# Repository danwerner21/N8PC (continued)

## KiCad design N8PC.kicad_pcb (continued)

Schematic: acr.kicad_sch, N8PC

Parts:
R5: 470; STD_DDW_RESISTOR
U32: 74LS139; STD_DDW_DIP16
U39: 74LS04; STD_DDW_DIP14
U55: 74LS273; STD_DDW_DIP20
U70: 74LS174; STD_DDW_DIP16

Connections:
+5V: U55.20 (VCC), U70.16 (VCC); also elsewhere on the board
A1: U32.13 (A1); also elsewhere on the board
A15_ROM: U70.2 (Q0); also elsewhere on the board
A16_ROM: U70.5 (Q1); also elsewhere on the board
A17_ROM: U70.7 (Q2); also elsewhere on the board
A18_ROM: U70.10 (Q3); also elsewhere on the board
A19_ROM: U70.12 (Q4); also elsewhere on the board
ACR5: U55.15 (Q5); also elsewhere on the board
D0: U55.3 (D0), U70.3 (D0); also elsewhere on the board
D1: U55.4 (D1), U70.4 (D1); also elsewhere on the board
D2: U55.7 (D2), U70.6 (D2); also elsewhere on the board
D3: U55.8 (D3), U70.11 (D3); also elsewhere on the board
D4: U55.13 (D4), U70.13 (D4); also elsewhere on the board
D5: U55.14 (D5); also elsewhere on the board
D6: U55.17 (D6); also elsewhere on the board
D7: U55.18 (D7), U70.14 (D5); also elsewhere on the board
EXT-RES: U55.1 (~Mr), U70.1 (~Mr); also elsewhere on the board
GND: U55.10 (GND), U70.8 (GND); also elsewhere on the board
LED0: U55.2 (Q0); also elsewhere on the board
LED1: U55.5 (Q1); also elsewhere on the board
LED2: U55.6 (Q2); also elsewhere on the board
LED3: U70.15 (Q5); also elsewhere on the board
unnamed: R5.1, U39.4
unnamed: U32.12 (O0), U55.11 (Cp)
unnamed: U32.10 (O2), U70.9 (Cp)
RTS_TTL1: U55.16 (Q6); also elsewhere on the board
STATUS-LED: R5.2; also elsewhere on the board
/ACRCS: U32.15 (E); also elsewhere on the board
/RESAY3: U55.12 (Q4); also elsewhere on the board
/ROM_ENABLE: U55.19 (Q7); also elsewhere on the board
/STATUS: U39.3, U55.9 (Q3)
/WR: U32.14 (A0); also elsewhere on the board

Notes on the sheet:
STATUS LED
AUXILIARY CONTROL REGISTER

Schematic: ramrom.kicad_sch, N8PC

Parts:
K3, K4, K5, K16, K18: CONN_3; STD_DDW_PINHEAD_V_1x03
U13: 27C080; STD_DDW_DIP32
U53: SRAM_512KO; STD_DDW_DIP32

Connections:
+5V: K3.3, K16.3, K18.3, U13.32 (VCC), U53.32 (VCC); also elsewhere on the board
A0: U13.12 (A0), U53.12 (A0); also elsewhere on the board
A1: U13.11 (A1), U53.11 (A1); also elsewhere on the board
A2: U13.10 (A2), U53.10 (A2); also elsewhere on the board
A3: U13.9 (A3), U53.9 (A3); also elsewhere on the board
A4: U13.8 (A4), U53.8 (A4); also elsewhere on the board
A5: U13.7 (A5), U53.7 (A5); also elsewhere on the board
A6: U13.6 (A6), U53.6 (A6); also elsewhere on the board
A7: U13.5 (A7), U53.5 (A7); also elsewhere on the board
A8: U13.27 (A8), U53.27 (A8); also elsewhere on the board
A9: U13.26 (A9), U53.26 (A9); also elsewhere on the board
A10: U13.23 (A10), U53.23 (A10); also elsewhere on the board
A11: U13.25 (A11), U53.25 (A11); also elsewhere on the board
A12: U13.4 (A12), U53.4 (A12); also elsewhere on the board
A13: U13.28 (A13), U53.28 (A13); also elsewhere on the board
A14: U13.29 (A14), U53.3 (A14); also elsewhere on the board
A15: U53.31 (A15); also elsewhere on the board
A15_ROM: K18.1; also elsewhere on the board
A16: U53.2 (A16); also elsewhere on the board
A16_ROM: U13.2 (A16); also elsewhere on the board
A17: K16.1; also elsewhere on the board
A17_ROM: K3.1; also elsewhere on the board
A18: U53.1 (A18); also elsewhere on the board
A18_ROM: K4.1, K5.3; also elsewhere on the board
A19_ROM: K5.1; also elsewhere on the board
D0: U13.13 (D0), U53.13 (DQ0); also elsewhere on the board
D1: U13.14 (D1), U53.14 (DQ1); also elsewhere on the board
D2: U13.15 (D2), U53.15 (DQ2); also elsewhere on the board
D3: U13.17 (D3), U53.17 (DQ3); also elsewhere on the board
D4: U13.18 (D4), U53.18 (DQ4); also elsewhere on the board
D5: U13.19 (D5), U53.19 (DQ5); also elsewhere on the board
D6: U13.20 (D6), U53.20 (DQ6); also elsewhere on the board
D7: U13.21 (D7), U53.21 (DQ7); also elsewhere on the board
GND: U13.16 (GND), U53.16 (VSS); also elsewhere on the board
unnamed: K3.2, U13.30 (A17)
unnamed: K4.2, U13.31 (A18)
unnamed: K5.2, U13.1 (A19)
unnamed: K16.2, U53.30 (A17)
unnamed: K18.2, U13.3 (A15)
/CS_RAMLO: U53.22 (CE#); also elsewhere on the board
/CS_ROM: U13.22 (~CE); also elsewhere on the board
/RD: U13.24 (~OE), U53.24 (OE#); also elsewhere on the board
/WR: K4.3, U53.29 (WE#); also elsewhere on the board

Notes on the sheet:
K3 = USE FOR 32 PIN EPROM OR 28 PIN EPROM K4 = USE FOR 27C080 EPROM OR 29C040 FLASH K5 = USE FOR 27C080 EPROM OR 29C040 FLASH K18 = USE FOR 32 PIN EPROM OR 28 PIN EPROM
K16 = USE FOR 512K SRAM OR 128K SRAM

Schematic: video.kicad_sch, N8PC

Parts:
C34: 4.7pF; STD_DDW_CAP
D5: 1N5817; STD_DDW_DIODE
J11: F18A TANG NANO Connector; STD_DDW_PinHeader_2x10
U18: 74LS32; STD_DDW_DIP14
U23: TMS9918 EMU; STD_DDW_DIP40

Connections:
+5V: D5.2 (A), U23.33 (VCC); also elsewhere on the board
A0: C34.1, J11.14, U23.13 (MODE); also elsewhere on the board
D0: J11.19, U23.17 (CD7); also elsewhere on the board
D1: J11.17, U23.18 (CD6); also elsewhere on the board
D2: J11.15, U23.19 (CD5); also elsewhere on the board
D3: J11.13, U23.20 (CD4); also elsewhere on the board
D4: J11.11, U23.21 (CD3); also elsewhere on the board
D5: J11.9, U23.22 (CD2); also elsewhere on the board
D6: J11.7, U23.23 (CD1); also elsewhere on the board
D7: J11.5, U23.24 (CD0); also elsewhere on the board
EXT-RES: J11.12, U23.34 (~RESET); also elsewhere on the board
GND: C34.2, J11.1, J11.3, U23.12 (GND); also elsewhere on the board
unnamed: D5.1 (K), J11.2
VRY: J11.4, U23.38 (CPUCLK); also elsewhere on the board
/RD: U18.13; also elsewhere on the board
/VDPCS: U18.9, U18.12; also elsewhere on the board
/VDPRD: J11.18, U18.11, U23.15 (~CSR)
/VDPWR: J11.16, U18.8, U23.14 (~CSW)
/VINT: U23.16 (~INT); also elsewhere on the board
/WR: U18.10; also elsewhere on the board

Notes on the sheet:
Connector for Tang Nano F18A emulator https://github.com/lfantoniosi/tn_vdp
TMS9918 Socket, suitable for a Pico99 or F18A TMS9918 emulator Not suitable for an actual TMS9918 chip.

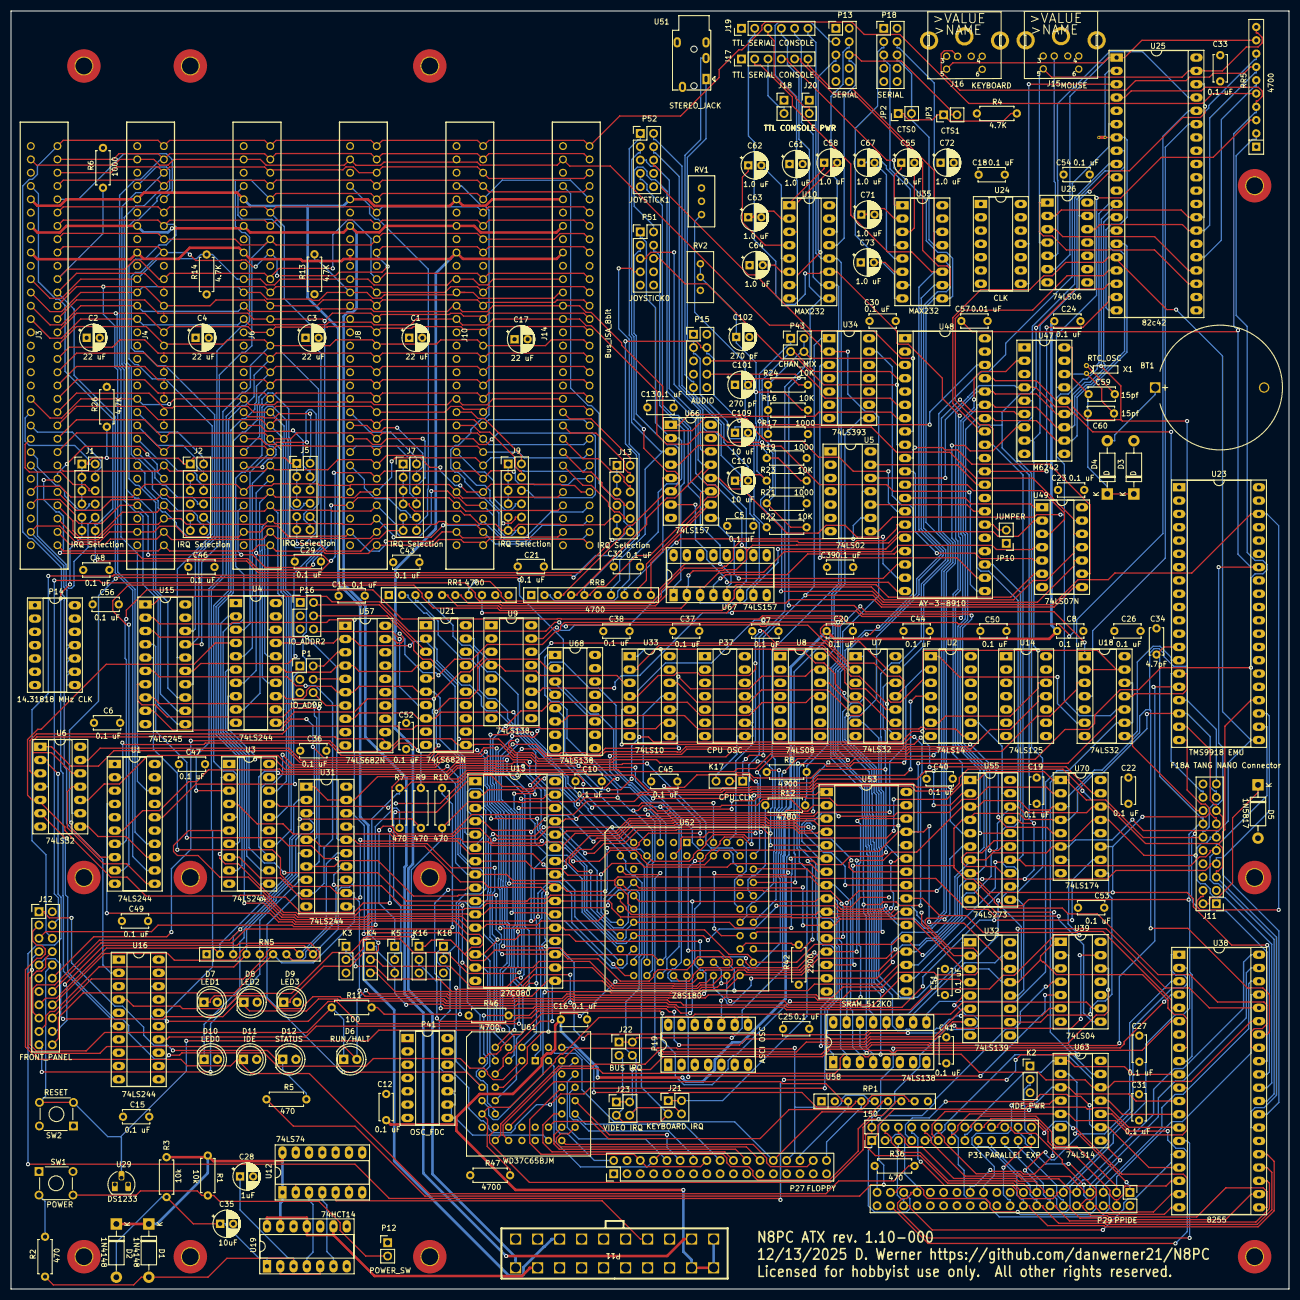
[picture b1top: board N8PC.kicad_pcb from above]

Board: 4 copper layers, 244.0 x 244.0 mm, 226 parts (0 on the bottom side), 364 nets.

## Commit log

2025-11-03 n8pc
2025-11-30 rev 1.0
2025-12-14 V1.1 PCB and schematic fix issue with data direction for bus
2025-12-14 update for front panel fix
2026-01-03 add photos
